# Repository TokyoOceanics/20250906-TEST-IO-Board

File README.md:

# 20250906-TEST-IO-Board
GPIOプログラミング入門用の回路基板（KiCAD練習も兼ねる）

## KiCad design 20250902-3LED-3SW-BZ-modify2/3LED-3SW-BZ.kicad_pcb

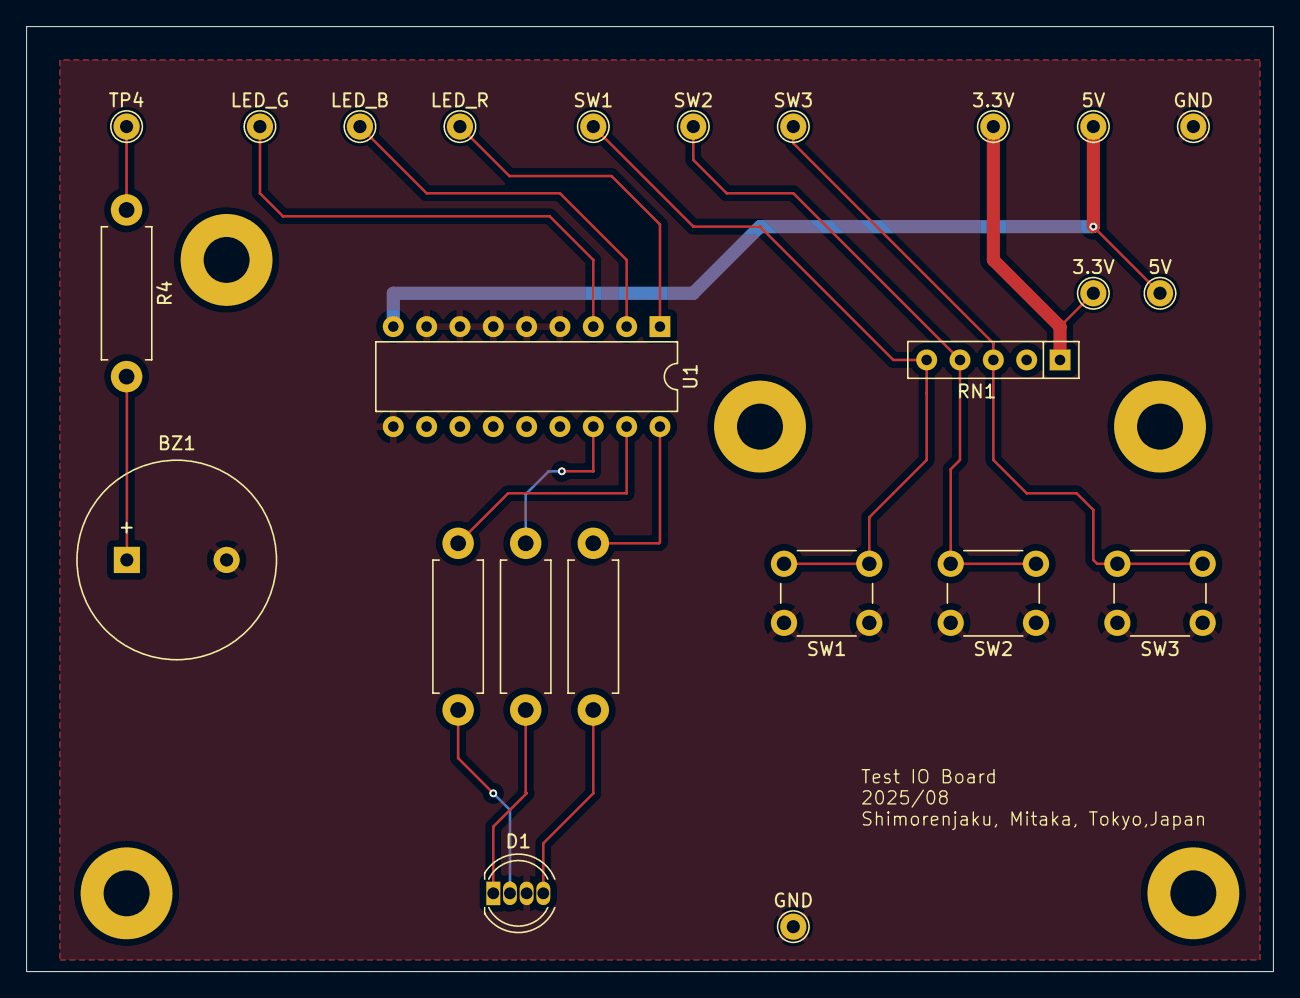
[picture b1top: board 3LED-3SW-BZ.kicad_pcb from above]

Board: 2 copper layers, 95.0 x 72.0 mm, 24 parts (0 on the bottom side), 17 nets.

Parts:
3.3V, 3.3V#2: 3.3V; TestPoint_THTPad_D2.0mm_Drill1.0mm
5V, 5V#2: 5V; TestPoint_THTPad_D2.0mm_Drill1.0mm
BZ1: Buzzer; Buzzer_15x7.5RM7.6
D1: LED_GBKR; LED_D5.0mm-4_RGB
GND: GND; TestPoint_THTPad_D2.0mm_Drill1.0mm
GND#2: GND; TestPoint_THTPad_D2.0mm_Drill1.0mm
LED_B: LED_B; TestPoint_THTPad_D2.0mm_Drill1.0mm
LED_G: LED_G; TestPoint_THTPad_D2.0mm_Drill1.0mm
LED_R: LED_R; TestPoint_THTPad_D2.0mm_Drill1.0mm
R1, R2, R3, R4: R; R_Axial_DIN0411_L9.9mm_D3.6mm_P12.70mm_Horizontal
RN1: R_Network04; R_Array_SIP5
SW1: SW1; TestPoint_THTPad_D2.0mm_Drill1.0mm
SW1#2: RED; SW_PUSH_6mm_H7.3mm
SW2: GREEN; SW_PUSH_6mm_H7.3mm
SW2#2: SW2; TestPoint_THTPad_D2.0mm_Drill1.0mm
SW3: BLUE; SW_PUSH_6mm_H7.3mm
SW3#2: SW3; TestPoint_THTPad_D2.0mm_Drill1.0mm
TP4: BUZ; TestPoint_THTPad_D2.0mm_Drill1.0mm
U1: TBD62785APG; DIP-18_W7.62mm

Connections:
+3.3V: 3.3V.1, 3.3V#2.1, RN1.1 (common)
+5V: 5V.1, 5V#2.1, U1.9 (VCC)
GND: BZ1.2 (-), D1.3 (K), GND.1, GND#2.1, SW1#2.1, SW2.1, SW3.1, U1.4 (I4), U1.5 (I5), U1.6 (I6), U1.7 (I7), U1.8 (I8), U1.10 (GND)
unnamed: BZ1.1 (+), R4.2
unnamed: D1.2 (BA), R3.2
unnamed: D1.1 (GA), R2.2
unnamed: D1.4 (RA), R1.2
unnamed: R4.1, TP4.1
unnamed: RN1.3 (R2), SW3.2, SW3#2.1
unnamed: RN1.4 (R3), SW2.2, SW2#2.1
unnamed: RN1.5 (R4), SW1.1, SW1#2.2
unnamed: LED_R.1, U1.1 (I1)
unnamed: LED_B.1, U1.2 (I2)
unnamed: LED_G.1, U1.3 (I3)
unnamed: R1.1, U1.18 (O1)
unnamed: R3.1, U1.17 (O2)
unnamed: R2.1, U1.16 (O3)
